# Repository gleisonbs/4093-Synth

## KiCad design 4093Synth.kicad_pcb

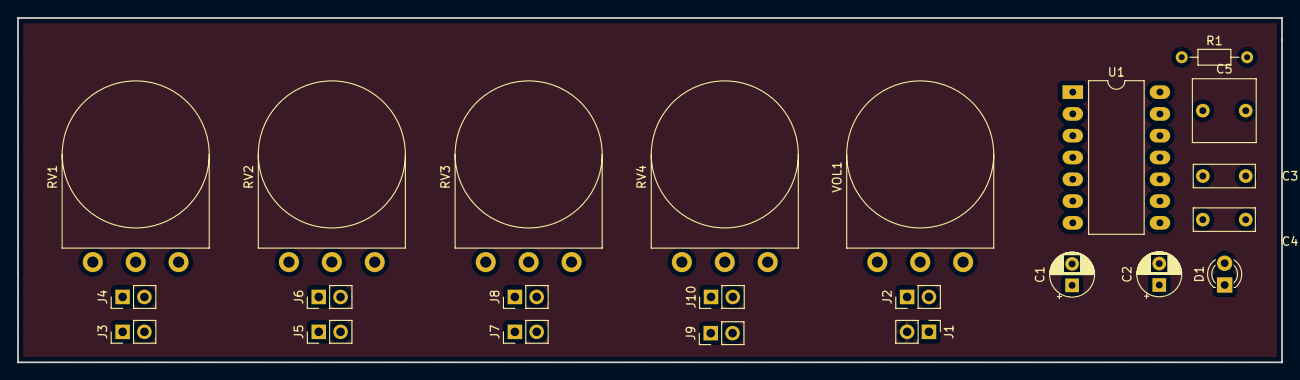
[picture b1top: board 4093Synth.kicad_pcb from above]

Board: 2 copper layers, 147.3 x 40.1 mm, 23 parts (0 on the bottom side), 20 nets, no tracks yet.

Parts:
C1: 10uF; CP_Radial_D5.0mm_P2.50mm
C2: 2.2uF; CP_Radial_D5.0mm_P2.50mm
C3: 100nF; C_Rect_L7.0mm_W2.5mm_P5.00mm
C4: 10nF; C_Rect_L7.0mm_W2.5mm_P5.00mm
C5: 1uF; C_Rect_L7.2mm_W7.2mm_P5.00mm_FKS2_FKP2_MKS2_MKP2
D1: LED; LED_D3.0mm
J1, J2, J3, J4, J5, J6, J7, J8, J9, J10: Conn_01x02_Female; PinHeader_1x02_P2.54mm_Vertical
R1: 600; R_Axial_DIN0204_L3.6mm_D1.6mm_P7.62mm_Horizontal
RV1, RV2, RV3, RV4: R_POT; Potentiometer_Omeg_PC16BU_Vertical
U1: HEF4093B; DIP-14_W10.16mm_LongPads
VOL1: 100kA; Potentiometer_Omeg_PC16BU_Vertical

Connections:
GND: C1.2, C2.2, C3.2, C4.2, C5.2, D1.1, J2.2, U1.7, VOL1.1
unnamed: C1.1, J3.2, U1.2
unnamed: C2.1, J5.2, U1.6
unnamed: C3.1, J7.2, U1.9
unnamed: C4.1, J9.2, U1.13
unnamed: C5.1, J9.1, R1.1, U1.11, VOL1.2
unnamed: D1.2, R1.2
unnamed: J1.1, U1.1, U1.14
unnamed: J2.1, VOL1.3
unnamed: J3.1, U1.3, U1.5
unnamed: J4.1, RV1.2, RV1.3
unnamed: J4.2, RV1.1
unnamed: J5.1, U1.4, U1.8
unnamed: J6.1, RV2.2, RV2.3
unnamed: J6.2, RV2.1
unnamed: J7.1, U1.10, U1.12
unnamed: J8.1, RV3.2, RV3.3
unnamed: J8.2, RV3.1
unnamed: J10.1, RV4.2, RV4.3
unnamed: J10.2, RV4.1

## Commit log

2018-10-14 Adds CV in for each Pot
